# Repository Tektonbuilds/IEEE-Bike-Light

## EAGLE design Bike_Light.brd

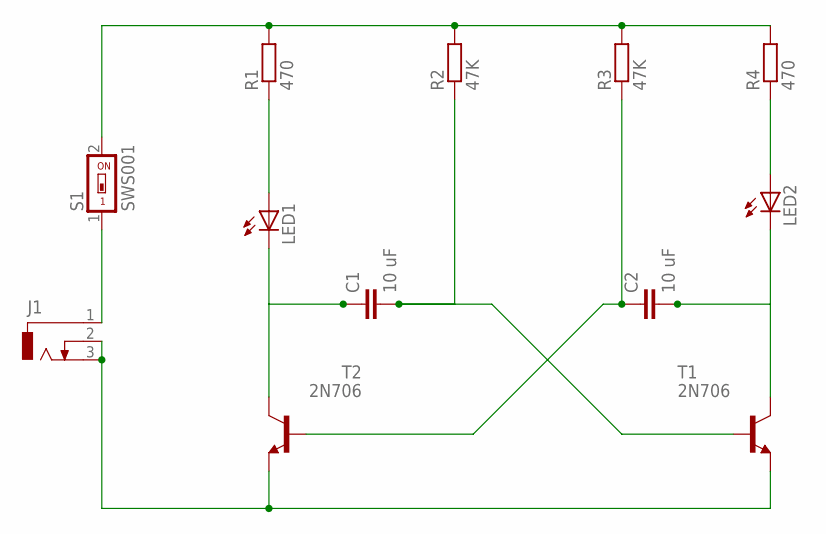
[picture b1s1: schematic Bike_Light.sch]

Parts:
C1, C2: 10 uF; C2.5-3
J1: DCJ0303
LED1, LED2: LED5MM
R1, R4: 470; 0207/10
R2, R3: 47K; 0207/10
S1: SWS001; SMS-001
T1, T2: 2N706; TO18

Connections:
unnamed: R1.2, R2.2, R3.2, R4.2, S1.2
unnamed: LED1.A, R1.1
unnamed: C1.1, LED1.K (C), T2.3 (C)
unnamed: C1.2, R2.1, T1.2 (B)
unnamed: C2.1, R3.1, T2.2 (B)
unnamed: LED2.A, R4.1
unnamed: C2.2, LED2.K (C), T1.3 (C)
unnamed: J1.1, S1.1
unnamed: J1.2, J1.3, T1.1 (E), T2.1 (E)

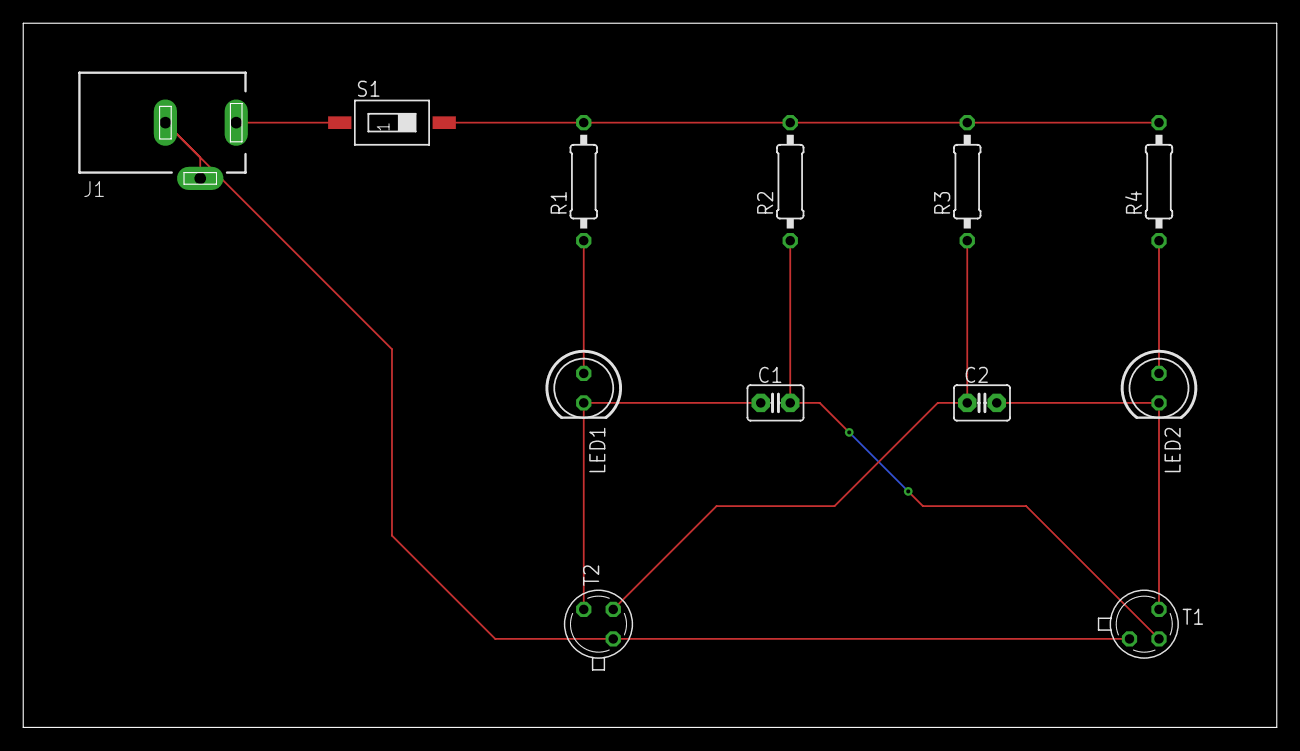
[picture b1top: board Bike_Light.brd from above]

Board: 2 copper layers, 107.9 x 60.6 mm, 12 parts (0 on the bottom side), 9 nets.

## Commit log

2018-04-10 Adding all neccessary files.
2018-04-10 Moved Gerber files to Gerber folder.
2018-04-10 deleted gerber files.
